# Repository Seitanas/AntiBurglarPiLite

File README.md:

AntiBurglar-pi Lite  
=====  
  
Home security system, based on raspberry-pi.  
System monitors two security zones, two temperature zones. Uses gnokii to send sms via gsm phone or modem, activates
siren via relay.  
Also monitors status of powerline, reports if power is down.  
System control is done via SMS commands:  
  
<b>arm password</b> (e.g arm 1111) - system is armed instantly.  
<b>disarm password</b> - armed system deactivates after receiving SMS.  
<b>status password</b> - system responds with device uptime and temperature status after receiving SMS.  
<b>siren on password</b> - siren is turned on.  
<b>siren off password</b> - siren is turned off.  
  
When triggered, alarm warning is sent do a predefined number in config.h file.  
  
Edit src/config.h and /boot/abp.conf to fit your needs.  
You need to install libgnokii development libraries, also wiringpi:  
http://wiringpi.com/download-and-install/  
Make sure to create /etc/gnokii.conf config file with configuration for your GSM modem or phone.  
Example of working gnokii.conf file with "Huawei Technologies Co., Ltd. E220 HSDPA Modem / E230/E270/E870 HSDPA/HSUPA" modem:  
  
    [global]
    model = AT
    port = /dev/ttyUSB0
    connection = serial

To build and install system
    make
    make install

If using raspbian distribution, copy init script from debian_init folder  
to /etc/init.d/ folder.  
Start antiburglar-pi with /etc/init.d/abp start

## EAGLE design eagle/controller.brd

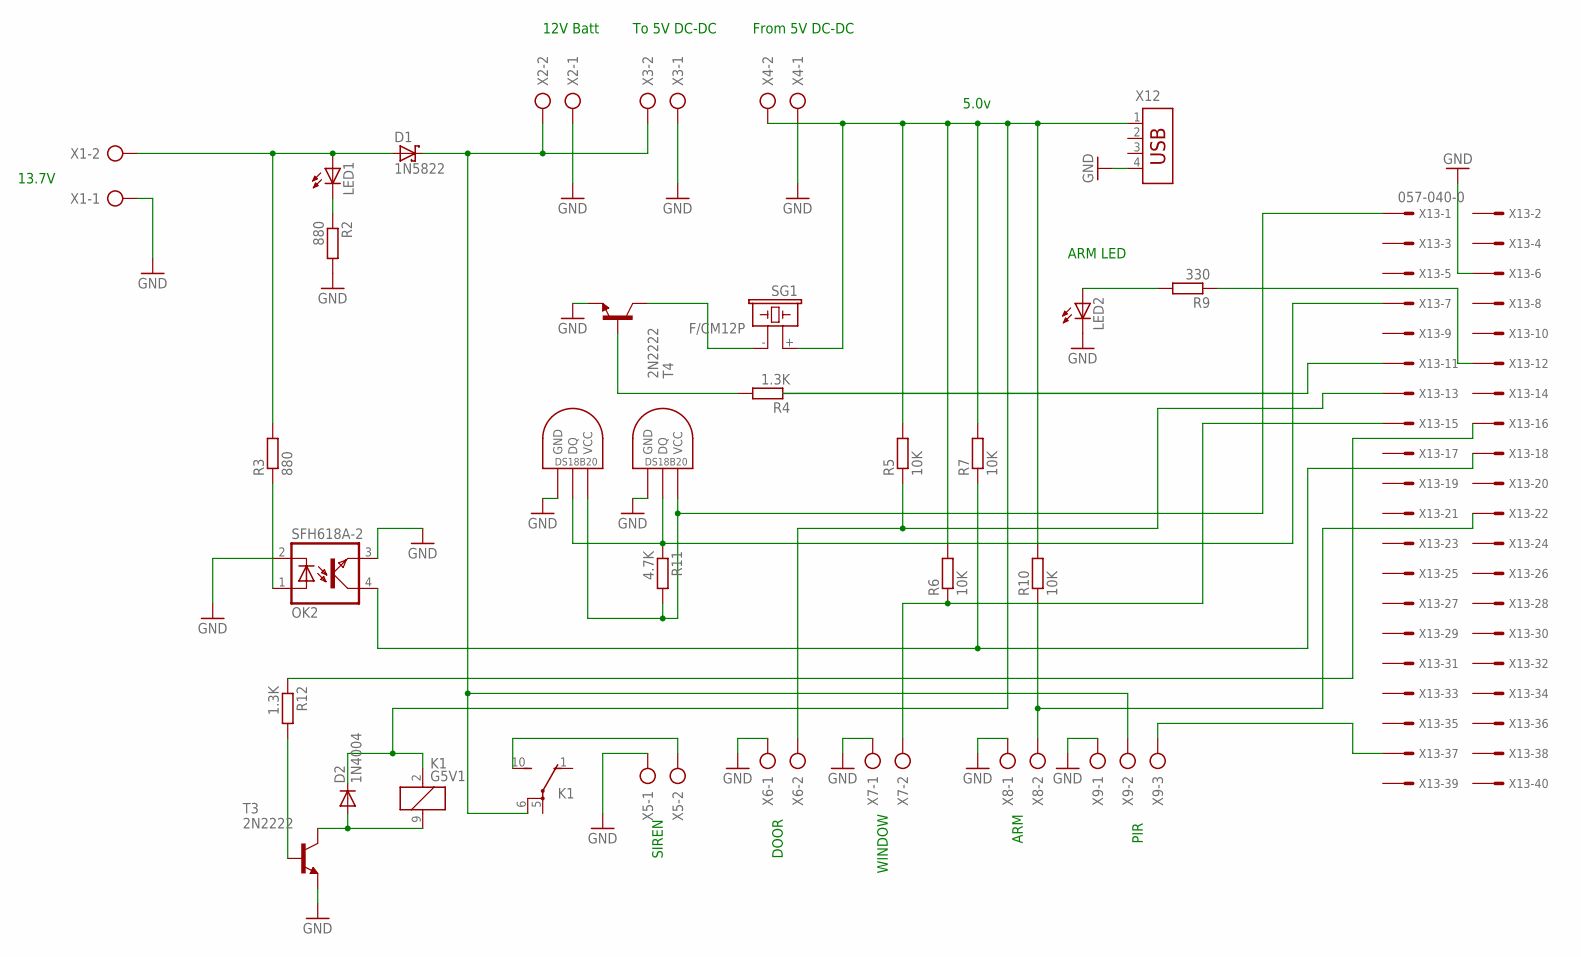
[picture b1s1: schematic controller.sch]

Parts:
D1: 1N5822; DO201T15
D2: 1N4004; DO41-10
K1: G5V1
LED1, LED2: LED5MM
OK2: SFH618A-2; DIP4
R2, R3: 880; 0204/7
R4, R12: 1.3K; 0204/7
R5, R6, R7, R10: 10K; 0204/7
R9: 330; 0204/7
R11: 4.7K; 0204/7
SG1: F/CM12P
T3, T4: 2N2222; TO92-EBC
U$1, U$2: DS1820TO92; DS1820
X1, X2, X3, X4, X5, X6, X7, X8: AK500/2
X9: AK500/3-H
X12: USB-787616; USB
X13: 057-040-0

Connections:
GND: LED2.K (C), OK2.2 (C), OK2.3 (EMIT), R2.2, T3.E, T4.E, U$1.GND, U$2.GND, X1.1, X2.1, X3.1, X4.1, X5.1, X6.1, X7.1, X8.1, X9.1, X12.4, X13.6
unnamed: D1.A, LED1.A, R3.2, X1.2
unnamed: R12.2, T3.B
unnamed: D2.A, K1.9 (2), T3.C
unnamed: D1.C, K1.6, X2.2, X3.2, X9.2
unnamed: X9.3, X13.37
unnamed: R4.1, X13.11
unnamed: LED1.K (C), R2.1
unnamed: OK2.1 (A), R3.1
unnamed: OK2.4 (COL), R7.1, X13.18
unnamed: R4.2, T4.B
unnamed: SG1.- (2), T4.C
unnamed: R5.1, X6.2, X13.13
unnamed: R6.1, X7.2, X13.15
unnamed: LED2.A, R9.2
unnamed: R9.1, X13.12
unnamed: R10.1, X8.2, X13.22
unnamed: R11.1, U$1.DQ, U$2.DQ, X13.7
unnamed: R11.2, U$1.VDD (VCC), U$2.VDD (VCC), X13.1
unnamed: R12.1, X13.16
unnamed: D2.C, K1.2 (1), R5.2, R6.2, R7.2, R10.2, SG1.+ (1), X4.2, X12.1
unnamed: K1.10 (S), X5.2

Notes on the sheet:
5.0v
DOOR
WINDOW
ARM
ARM LED
13.7V
SIREN
12V Batt
To 5V DC-DC
From 5V DC-DC
PIR

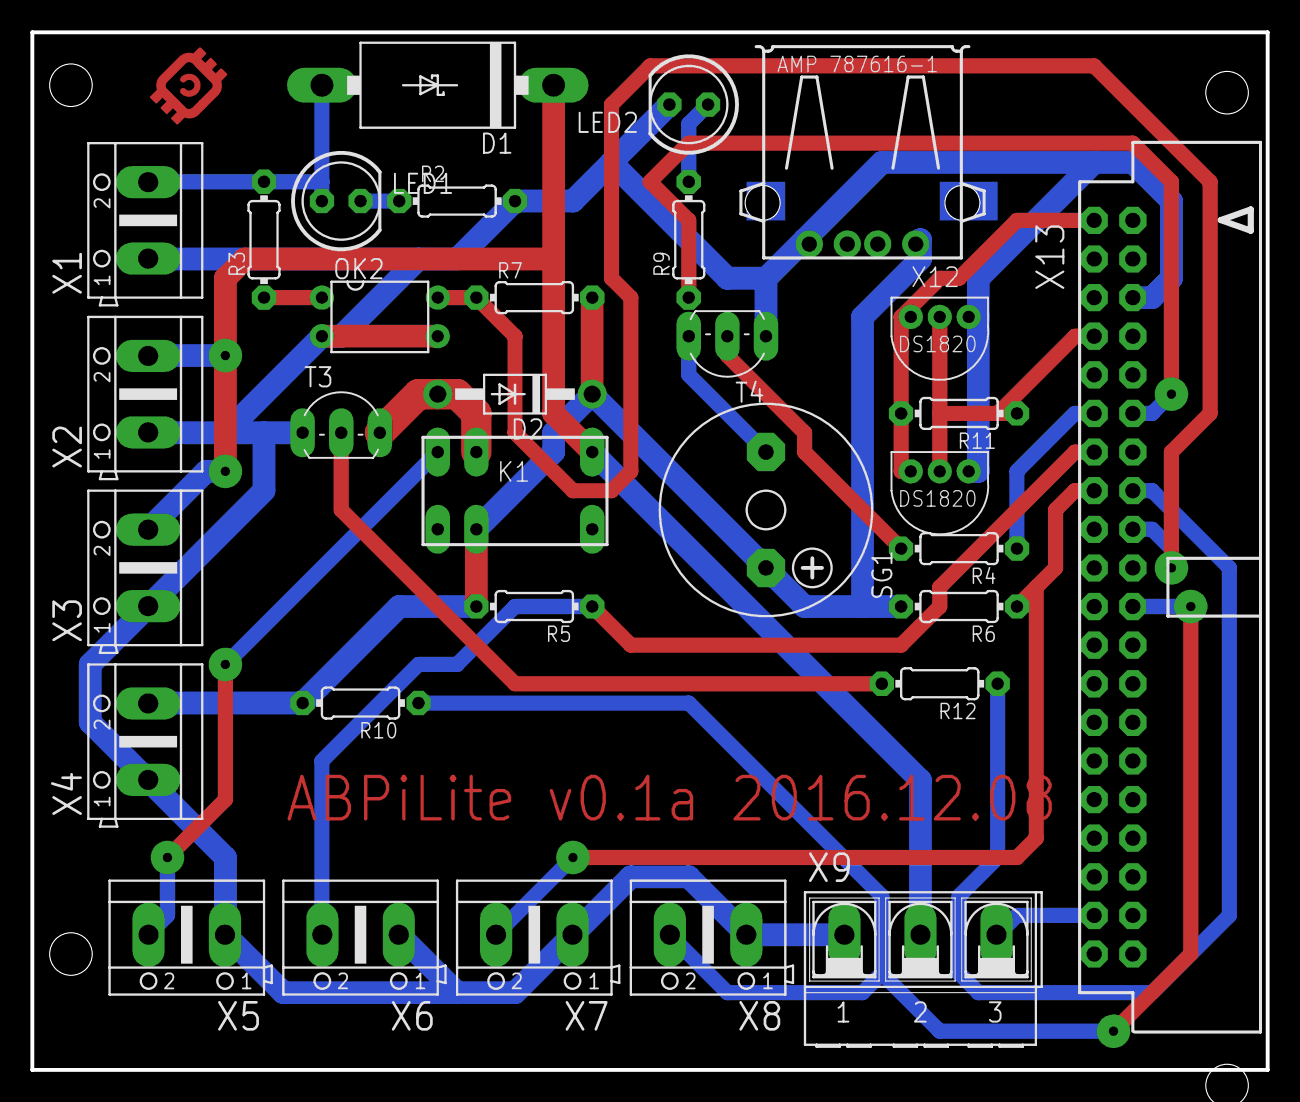
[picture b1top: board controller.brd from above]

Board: 2 copper layers, 81.3 x 68.2 mm, 33 parts (0 on the bottom side), 22 nets.

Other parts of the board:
U$3: OPEN_HARDWARE_LOGO

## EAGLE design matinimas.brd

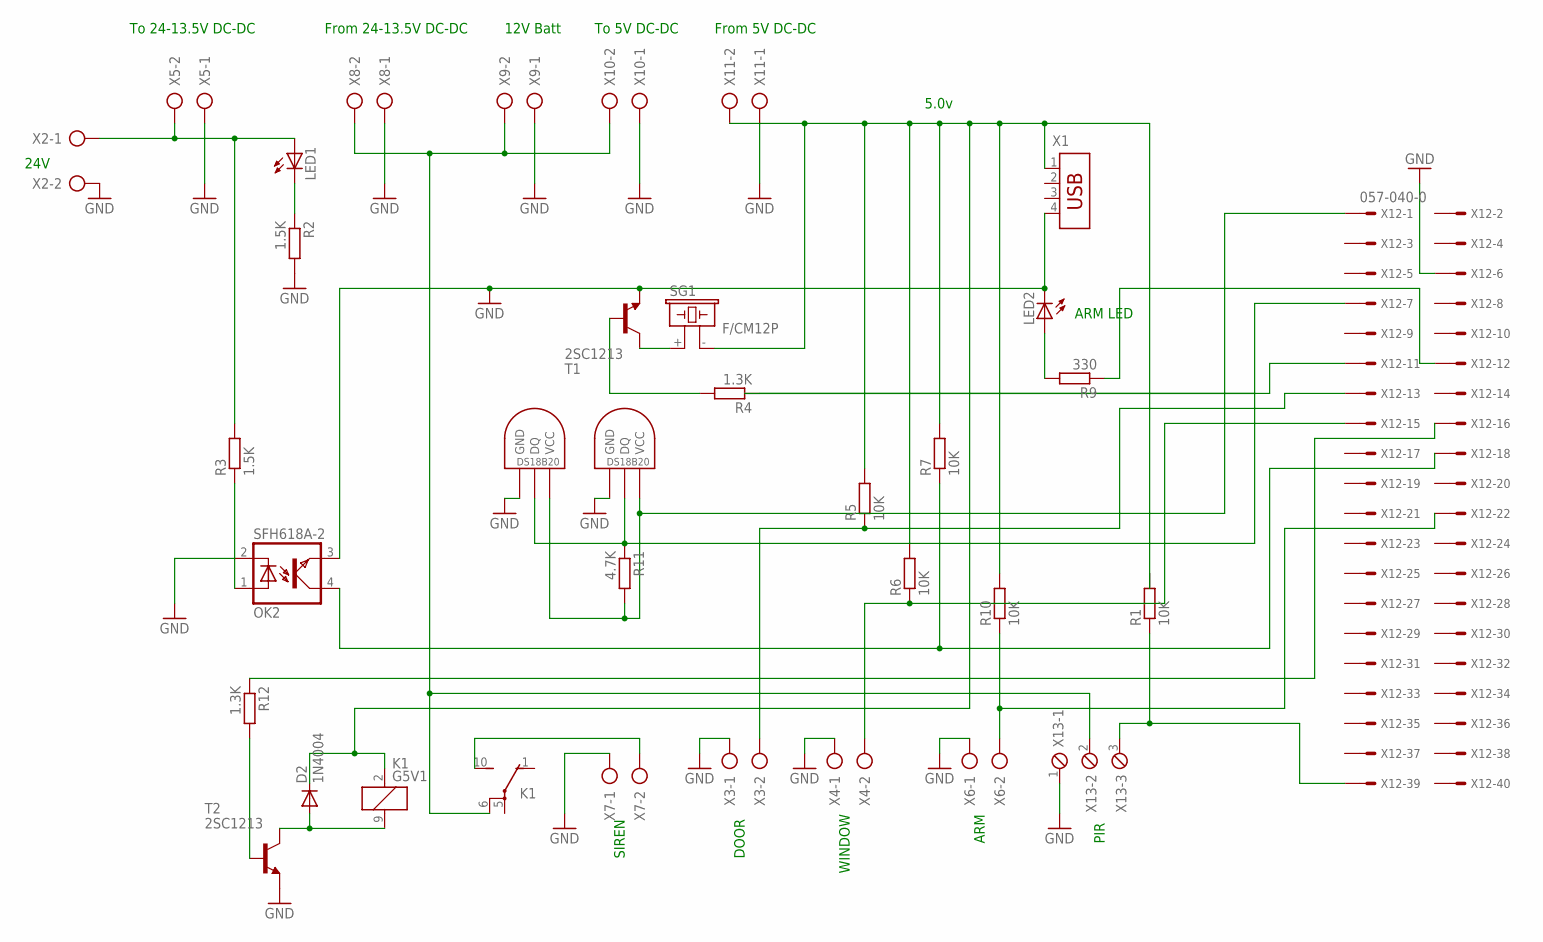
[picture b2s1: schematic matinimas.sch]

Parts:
D2: 1N4004; DO41-10
K1: G5V1
LED1, LED2: LED5MM
OK2: SFH618A-2; DIP4
R1, R5, R6, R7, R10: 10K; 0204/7
R2, R3: 1.5K; 0204/7
R4, R12: 1.3K; 0204/7
R9: 330; 0204/7
R11: 4.7K; 0204/7
SG1: F/CM12P
T1, T2: 2SC1213; TO92-EBC
U$1, U$2: DS1820TO92; DS1820
X1: USB-787616; USB
X2, X3, X4, X5, X6, X7, X8, X9, X10, X11: AK500/2
X12: 057-040-0
X13: MPT3; 3POL254

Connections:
GND: LED2.K (C), OK2.2 (C), OK2.3 (EMIT), R2.2, T1.E, T2.E, U$1.GND, U$2.GND, X1.4, X2.2, X3.1, X4.1, X5.1, X6.1, X7.1, X8.1, X9.1, X10.1, X11.1, X12.6, X13.1
unnamed: LED1.A, R3.2, X2.1, X5.2
unnamed: R12.2, T2.B
unnamed: D2.A, K1.9 (2), T2.C
unnamed: K1.6, X8.2, X9.2, X10.2, X13.2
unnamed: R1.1, X12.39, X13.3
unnamed: R4.1, X12.11
unnamed: LED1.K (C), R2.1
unnamed: OK2.1 (A), R3.1
unnamed: OK2.4 (COL), R7.1, X12.18
unnamed: R4.2, T1.B
unnamed: SG1.+ (1), T1.C
unnamed: R5.1, X3.2, X12.13
unnamed: R6.1, X4.2, X12.15
unnamed: LED2.A, R9.2
unnamed: R9.1, X12.12
unnamed: R10.1, X6.2, X12.22
unnamed: R11.1, U$1.DQ, U$2.DQ, X12.7
unnamed: R11.2, U$1.VDD (VCC), U$2.VDD (VCC), X12.1
unnamed: R12.1, X12.16
unnamed: D2.C, K1.2 (1), R5.2, R6.2, R7.2, R10.2, SG1.- (2), X1.1, X11.2
unnamed: K1.10 (S), X7.2

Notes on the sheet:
5.0v
DOOR
WINDOW
ARM
ARM LED
24V
SIREN
To 24-13.5V DC-DC
From 24-13.5V DC-DC
12V Batt
To 5V DC-DC
From 5V DC-DC
PIR

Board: 2 copper layers, 34 parts (0 on the bottom side), 22 nets, no tracks yet.

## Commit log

2016-11-11 First PCB
2016-11-12 Updating PIR
2016-11-12 First production release
2016-11-30 Fixing schematic bug
2016-12-01 Small redesign. Bugfixes
2016-12-01 Board update
2016-12-08 Optimising board
2016-12-21 Commiting application
2016-12-21 Updating readme
2016-12-21 Adding motion sersor info to replies
2016-12-21 Moving to systemd startup
2016-12-22 Fixing config file
2017-05-30 Create LICENSE
